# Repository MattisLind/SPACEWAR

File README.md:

# SPACEWAR

The original [Spacewar!](https://en.wikipedia.org/wiki/Spacewar!) game was written for the PDP-1 minicomputer and there were several ports to other architectures.

This port to the PDP-11 architecture was done by Bill Seiler & Larry Bryant in 1974. It was then submitted to DECUS as 11-192. 

SPACEWAR on the HP 1332A vector screen.

Click to see video clip:

SPACEWAR on a VR12 vector screen. Has a very nice P7 phosphor that has fantastic after-glow. Actually this type of phosphor was used in the PDP-1 screen which the original SPACEWAR was run on.

Ufortunatley DECUS threw away all the sources many years ago. By luck I got in contact with Bill Seiler and he sent me the source files. The sources were provided to me as scanned documents. With some help the original PDFs were tidied up to help the OCR process. Then I partly OCRed and manually transcribed all files into text files.
The files were then then fed into the PAL11-S assembler and numerous errors were detected already when trying to get the files pass the syntax check. Then the output listing files was compared side by side with the original scanned files. Byte for byte were checked and yet more problems were found. Finally during linking a number of issues with global symbols were found. In the end the program assembled and linked correctly.

As a side note there exists at least two more ports of the SPACEWAR game to the PDP-11 architecture ([for example this one](https://saildart.org/SW.P11%5B11,BO%5D)), but both of those rely on the VT11 vector drawing option which is for example present in the GT40 system. I don't have a VT11 neither a GT40 so this is my best option to get SPACEWAR on a PDP-11.

## Give it to me!

If you don't want to go down the route of assembling and linking all the source moddules there is an easy solution. Just grab the dddp.dsk image and use the TU58FS tool (or some other TU58 emulator) to serve it to your PDP-11.  It contains a bootable DDDP image with a SPACEWAR image binary image. Just type R SPCWAR.LDA and it will run provided you have the AR11 card.

## Assembling

In case you just want to run the binary and not want the fun of building it from scratch, just grab the SPACEWAR.ABS file in the ar11-patch branch (if you have a AR11 board in your machine) and run in from ~~025424~~ ~~025432 (please note that this may change since a new build of the code might affect the entrypoint, check the SPACEWAR.MAP file when in doubt). Make sure to also load the IOX binary in the IOX-11 subfolder into memory before starting the SPACEWAR and set the switch regsiter to all zeroes. I have seen that otherwise it gets stuck in the IOX library. Probably a non-zero SR indicate some options to the IOX library, but I haven't investigated that further.~~
Update: Even easier should be to use the SPACEWARWIOX.LDA binary since it includes the IOX-11 binary and also have the proper transfer address which should make the loader start it directly. Make sure to have the SR set to 0. This binary starts at 1000 if it is loaded using PDP11GUI rather than read from paper tape.

It is possible to assemble the files located in the SRC folder using PAL11-S assembler under SimH PDP-11 simulator. PAL11-S is part of the [PDP-11 Paper Tape Software](http://bitsavers.informatik.uni-stuttgart.de/www.computer.museum.uq.edu.au/pdf/DEC-11-XPTSA-B-D%20PDP-11%20Paper%20Tape%20Software%20Handbook.pdf). 

First toggle in the bootstrap loader (or use the file TOOLS/simh.ini)
```
sim> SET CPU 11/05
Disabling XQ
sim> SET CPU 16K
sim> 
sim> 
sim> ; Disable devices that we don't need
sim> SET HK DISABLE
sim> SET DZ DISABLE
sim> SET RL DISABLE
sim> SET RX DISABLE
sim> SET RP DISABLE
sim> SET RQ DISABLE
sim> SET TM DISABLE
sim> SET TQ DISABLE
sim> SET RK DISABLE
sim> 
sim> ; Enable the high-speed paper tape reader/punch
sim> SET PTR ENABLE
sim> SET PTP ENABLE
sim> DEPOSIT 037744 016701
sim> DEPOSIT 037746 000026
sim> DEPOSIT 037750 012702
sim> DEPOSIT 037752 000352
sim> DEPOSIT 037754 005211
sim> DEPOSIT 037756 105711
sim> DEPOSIT 037760 100376
sim> DEPOSIT 037762 116162
sim> DEPOSIT 037764 000002
sim> DEPOSIT 037766 037400
sim> DEPOSIT 037770 005267
sim> DEPOSIT 037772 177756
sim> DEPOSIT 037774 000765
sim> DEPOSIT 037776 177550
sim> ATTACH PTR TOOLS/DEC-11-L2PC-PO.ptap 
sim> GO 037744

HALT instruction, PC: 037500 (MOV PC,SP)
sim> D SR 37500 
sim> ATTACH PTR TOOLS/dec-uplsa-a-pl.bin 
PTR: unit is read only
sim> GO 037500

PAL-11S  V003A

*S 
```
Now pressing Ctrl-E allows for attaching the correct input and output virtual paper tapes.
```
Simulation stopped, PC: 035110 (CMPB R1,#14)
sim> attach ptr SRC/SPCWAR.PAL
sim> attach ptp OBJ/SPCWAR.OBJ
PTP: creating new file
sim> attach lpt LST/SPCWAR.LST
LPT: creating new file
sim> c
```
Now we are back in the PAL11-S assmebler. But it has alread greated you above with an S(ource) so it won't do that again. Simply type H for input via High-Speed reader. The same for the O(utput). Send L(ist) to the P(rinter) and the T(able) to the T(eletype) output.
```
H

*B H

*L P

*T T

 ADBR   = 176772 G     ADCS   = 176770 G     AMMO     000216RG  
 ANGH1    000154RG     ANGH2    000202RG     ANGL1    000152RG  
 ANGL2    000200RG     ANGMID = 000702 G     COMPAR = ****** G  
 DAC0   = 176750 G     DAC1   = 176752 G     DAC2   = 176754 G  
 FIRE   = 001440 G     FLAG1    000132RG     FLAG2    000160RG  
 GAME1    000222RG     GAME2    000224RG     GRAVTY = ****** G  
 GRVFLG   000226RG     HIT1     000204RG     HIT2     000206RG  
 MASK   = 002100 G     PARM   = ****** G     PC     =%000007    
 POINT  = ****** G     PTNUM  = ****** G     PTREP    000230RG  
 RESET  = ****** G     RKTSIZ = 007000 G     RKT1   = ****** G  
 RKT2   = ****** G     R0     =%000000       R1     =%000001    
 R2     =%000002       R3     =%000003       R4     =%000004    
 R5     =%000005       R6     =%000006       R7     =%000007    
 SHOTS1   000210RG     SHOTS2   000212RG     SP     =%000006    
 SPCRST   000020RG     SPCWAR   000000RG     SPC01    000066R   
 SUNSZ  = 004000 G     TSPEED   000220RG     UPDAT1 = ****** G  
 UPDAT2 = ****** G     WIN      000214RG     XDISP1   000150RG  
 XDISP2   000176RG     XSIZE1   000142RG     XSIZE2   000170RG  
 XVELH1   000146RG     XVELH2   000174RG     XVELL1   000144RG  
 XVELL2   000172RG     YDISP1   000140RG     YDISP2   000166RG  
 YSIZE1   000130RG     YSIZE2   000156RG     YVELH1   000136RG  
 YVELH2   000000RG     YVELL1   000134RG     YVELL2   000162RG  
 .      = 000232R     

 END ?
```

So now the assembler want to run the second pass which means that we have to load our virtual source tape again. Press Ctrl-E now to get into SimH.
```
Simulation stopped, PC: 035464 (BR 35334)
sim> attach ptr SRC/SPCWAR.PAL
sim> c
```
And then press return when back into the PAL11-S environment.

```

000000 ERRORS

PAL-11S  V003A

*S 
```
Do this for each and every file to produce object files.

## Linking

Linking involves running the LINK11-S which is similar to how to run the assembler.
```
sim> SET CPU 11/05
Disabling XQ
sim> SET CPU 16K
sim>  
sim> ; Disable devices that we don't need
sim> SET HK DISABLE
sim> SET DZ DISABLE
sim> SET RL DISABLE
sim> SET RX DISABLE
sim> SET RP DISABLE
sim> SET RQ DISABLE
sim> SET TM DISABLE
sim> SET TQ DISABLE
sim> SET RK DISABLE
sim> 
sim> ; Enable the high-speed paper tape reader/punch
sim> SET PTR ENABLE
sim> SET PTP ENABLE
sim> DEPOSIT 037744 016701
sim> DEPOSIT 037746 000026
sim> DEPOSIT 037750 012702
sim> DEPOSIT 037752 000352
sim> DEPOSIT 037754 005211
sim> DEPOSIT 037756 105711
sim> DEPOSIT 037760 100376
sim> DEPOSIT 037762 116162
sim> DEPOSIT 037764 000002
sim> DEPOSIT 037766 037400
sim> DEPOSIT 037770 005267
sim> DEPOSIT 037772 177756
sim> DEPOSIT 037774 000765
sim> DEPOSIT 037776 177550
sim> ATTACH PTR TOOLS/DEC-11-L2PC-PO.ptap 
sim> GO 037744

HALT instruction, PC: 037500 (MOV PC,SP)
sim> ATTACH PTR TOOLS/dec-11-ulksa-a-pl.bin 
PTR: unit is read only
sim> D SR 0
sim> GO 037500

LINK-11S V002A
*I H

*O H

*M P

*T 

*B 

PASS 1

* 
Simulation stopped, PC: 035140 (MOV R5,14(SP))
sim> ATTACH PTP SPACEWAR.ABS
sim> ATTACH LPT SPACEWAR.MAP
sim> ATTACH PTR OBJ/SPCWAR.OBJ 
```
To the linker you specify the I(input) and O(utput) deivce. H (High-speed) reader or L (Low-speed). Load map (M) is either not generated at all if pressing RETURN or by pressing H (High speed punch) or T(teletype), or P(Line Printer). The there are two questions (T and B) how the relocation should be done. Press RETURN for top of memory to both of those.

In this case I have chosen to have the resulting binary to be generated on the paper tape punch and the module map on the line printer.

After this each file is fed into the linker by attaching it to the reader and pressing RETURN at the * prompt. When all object files has been presented to the first pass of the linker you can press U a the * prompt to show the remaining undefined symbols. When all is done press E and the linker will print the load map and then start the seconds pass, requesting the same object files in the same order.

```
* U

* E

PASS 2

* 
Simulation stopped, PC: 035122 (ADD #34662,R2)
sim> ATTACH PTR FPMP-11/FPMP-11-SPACEWAR.OBJ
sim> c
```

When you supplied the last file you should be greated with another linker startup message.

```
LINK-11S V002A
*I 
```
Then you know that all is good and there should be a binary file and map file generated.

The first time I tried to run the linker was not succesful. After feeding all source modules unfortunatley I got two undefined symbols.
```
sim> c

* U
$ICI  
$ICO  

* 
```

These two subroutines are from the FPMP-11 package. Just adding one of the two pre-made FPMP-11 object files does not resolve the two undefined symbols.
[FPMP-11 documentation.](http://bitsavers.informatik.uni-stuttgart.de/www.computer.museum.uq.edu.au/pdf/DEC-11-NFPMA-C-D%20FPMP-11%20User's%20Manual.pdf)

Reading the manual a bit more revealed that the reason is that the two premade object files just contain a subset of the FPMP-11 package, not the $ICI and $ICO modules! To get those into the build one has to add a special file with defines for two variables used by the conditional build of the FPMP-11 packaged. By feeding this file
```
;******************************************************
;
;               CONDITIONAL SWITCHES 
;               FOR FPMP-11 PACKAGE
;               WHEN USED WITH SPACE WAR
;
       CND$24=1
       CND$25=1
       .EOT
```
before the six FPMP-11 source files I had a tailor made object paper tape with just the $ICI and $ICO symbols defined! 

Please note that the SPCWAR module has to be the first module and the POINT module the last module. See comments further below. All the other modules comes inbetween including the FPMP-11 library built previously.
 
~~This new object tape was then fed first into the linker, followed by all the 19 object paper tapes of SPACE WAR ending with the module POINT which has to be the last module.~~ And indeed the link completeted without any unresolved symbols this time.
This was the resulting MODULE MAP from LINK11-S:
```
* U

* E

LOAD MAP

TRANSFER ADDRESS: 000001
LOW LIMIT: 025424
HIGH LIMIT: 037460
**********
MODULE  SPCWAR
SECTION ENTRY   ADDRESS SIZE
<. ABS.>        000000  000000
<      >        025424  000232
        ADBR    170402
        ADCS    170400
        AMMO    025642
        ANGH1   025600
        ANGH2   025626
        ANGL1   025576
        ANGL2   025624
        ANGMID  000702
        DAC0    170412
        DAC1    170414
        DPCS    170410
        ERASE   010000
        FIRE    001440
        FLAG1   025556
        FLAG2   025604
        GAME1   025646
        GAME2   025650
        GRVFLG  025652
        HIT1    025630
        HIT2    025632
        MASK    002100
        PTREP   025654
        RKTSIZ  007000
        SHOTS1  025634
        SHOTS2  025636
        SPCRST  025444
        SPCWAR  025424
        SUNSZ   004000
        TSPEED  025644
        WIN     025640
        XDISP1  025574
        XDISP2  025622
        XSIZE1  025566
        XSIZE2  025614
        XVELH1  025572
        XVELH2  025620
        XVELL1  025570
        XVELL2  025616
        YDISP1  025564
        YDISP2  025612
        YSIZE1  025554
        YSIZE2  025602
        YVELH1  025562
        YVELH2  025610
        YVELL1  025560
        YVELL2  025606
**********
MODULE  CHAR  
SECTION ENTRY   ADDRESS SIZE
<      >        025656  000302
        CHAR    025656
**********
MODULE  CHRTAB
SECTION ENTRY   ADDRESS SIZE
<      >        026160  000606
        CHRTAB  026160
**********
MODULE  COMPAR
SECTION ENTRY   ADDRESS SIZE
<      >        026766  000444
        COMPAR  026766
**********
MODULE  EXPLOD
SECTION ENTRY   ADDRESS SIZE
<      >        027432  000330
        EXPLOD  027432
        EXPREP  027550
        EXPX    027556
        EXPY    027560
**********
MODULE  GRAVTY
SECTION ENTRY   ADDRESS SIZE
<      >        027762  000450
        GRAVTY  027762
**********
MODULE  MULPLY
SECTION ENTRY   ADDRESS SIZE
<      >        030432  000304
        MULPLY  030432
**********
MODULE  PARM  
SECTION ENTRY   ADDRESS SIZE
<      >        030736  001214
        PARM    030736
**********
MODULE  PWRUP 
SECTION ENTRY   ADDRESS SIZE
<      >        032152  000106
**********
MODULE  RESET 
SECTION ENTRY   ADDRESS SIZE
<      >        032260  000206
        CENTER  040000
        ORBIT   000400
        RESET   032260
        RES01   032446
**********
MODULE  RKT1  
SECTION ENTRY   ADDRESS SIZE
<      >        032466  000160
        RKT1    032466
**********
MODULE  RKT2  
SECTION ENTRY   ADDRESS SIZE
<      >        032646  000142
        RKT2    032646
**********
MODULE  SCORE 
SECTION ENTRY   ADDRESS SIZE
<      >        033010  000266
        SCORE   033010
**********
MODULE  SINCOS
SECTION ENTRY   ADDRESS SIZE
<      >        033276  000462
        SINCOS  033276
**********
MODULE  SLINE 
SECTION ENTRY   ADDRESS SIZE
<      >        033760  000140
        SLINE   033760
**********
MODULE  SUN   
SECTION ENTRY   ADDRESS SIZE
<      >        034120  000304
        SUN     034120
**********
MODULE  UPDAT1
SECTION ENTRY   ADDRESS SIZE
<      >        034424  000372
        UPDAT1  034424
**********
MODULE  UPDAT2
SECTION ENTRY   ADDRESS SIZE
<      >        035016  000372
        UPDAT2  035016
**********
MODULE  FPMP11
SECTION ENTRY   ADDRESS SIZE
<      >        035410  000640
        $ERR    036212
        $ERRA   036222
        $ERVEC  036242
        $ICI    035416
        $ICO    035722
        $OCI    035410
        $OCO    035714
        $POLSH  036206
        $V20A   036206
**********
MODULE  POINT 
SECTION ENTRY   ADDRESS SIZE
<      >        036250  001210
        POINT   036250
        PTNUM   036456
PASS 2

* 
```
And it also resulted a 7323 byte file in Absolute Binary format! From the load map one can deduce the starting address of the binary. 025424 in this case.

### Full linking transcript

This the full transcript on how to link the SPACEWARWIOX.LDA binary. At the B prompt give 1000 to indicate that the starting address should be 1000 octal.

```
$ ~/simh/BIN/pdp11 

PDP-11 simulator V4.0-0 Beta        git commit id: f1a6d538
sim> do TOOLS/simh.ini
Disabling XQ

HALT instruction, PC: 037500 (MOV PC,SP)
sim> ATTACH PTR TOOLS/dec-11-ulksa-a-pl.bin 
sim> D SR 0
sim> GO 037500

LINK-11S V002A
*I H

*O H

*M P

*T 

*B 1000

PASS 1

* 
Simulation stopped, PC: 035122 (ADD #34662,R2)
sim> attach ptp SPACEWARWIOX.LDA
PTP: creating new file
sim> attach LPT SPACEWARWIOX.MAP
LPT: creating new file
sim> ATTACH PTR OBJ/SPCWAR.OBJ
sim> c

* 
Simulation stopped, PC: 035042 (MOV (SP)+,R5)
sim> ATTACH PTR FPMP-11/FPMP-11-SPACEWAR.OBJ
sim> c

* 
Simulation stopped, PC: 035036 (CLR R4)
sim> ATTACH PTR OBJ/CHAR.OBJ
sim> c

* 
Simulation stopped, PC: 035104 (CMPB R1,#14)
sim> ATTACH PTR OBJ/CHRTAB.OBJ
sim> c

* 
Simulation stopped, PC: 035110 (BHI 35354)
sim> ATTACH PTR OBJ/COMPAR.OBJ
sim> c

* 
Simulation stopped, PC: 035450 (JSR R4,35462)
sim> ATTACH PTR OBJ/EXPLOD.OBJ
sim> c

* 
Simulation stopped, PC: 035054 (MOV (SP)+,R0)
sim> ATTACH PTR OBJ/GRAVTY.OBJ
sim> c

* 
Simulation stopped, PC: 035122 (ADD #34662,R2)
sim> ATTACH PTR OBJ/MULPLY.OBJ
sim> c

* 
Simulation stopped, PC: 035140 (MOV R5,14(SP))
sim> ATTACH PTR OBJ/PARM.OBJ
sim> c

* ATTACH PTR OBJ/PWRUP.OBJ\\\\\\\\\\\\\\\\\\\\\\\\
Simulation stopped, PC: 035342 (ADD (SP)+,PC)
sim> ATTACH PTR OBJ/PWRUP.OBJ
sim> c

* 
Simulation stopped, PC: 035026 (MOV R3,-(SP))
sim> ATTACH PTR OBJ/RESET.OBJ
sim> c

* 
Simulation stopped, PC: 035342 (ADD (SP)+,PC)
sim> ATTACH PTR OBJ/RKT1.OBJ
sim> c

* 
Simulation stopped, PC: 035056 (RTI)
sim> ATTACH PTR OBJ/RKT2.OBJ
sim> c

* 
Simulation stopped, PC: 035460 (BR 35330)
sim> ATTACH PTR OBJ/SCORE.OBJ
sim> c

* 
Simulation stopped, PC: 032100 (BIT (R0)+,@4(SP))
sim> ATTACH PTR OBJ/SINCOS.OBJ
sim> c

* 
Simulation stopped, PC: 035110 (BHI 35354)
sim> ATTACH PTR OBJ/SLINE.OBJ
sim> C

* 
Simulation stopped, PC: 035336 (MOVB 34641(R1),(SP))
sim> ATTACH PTR OBJ/SUN.OBJ
sim> C

* 
Simulation stopped, PC: 035332 (ASL R1)
sim> ATTACH PTR OBJ/UPDAT1.OBJ
sim> C

* 
Simulation stopped, PC: 035336 (MOVB 34641(R1),(SP))
sim> ATTACH PTR OBJ/UPDAT2.OBJ
sim> C

* 
Simulation stopped, PC: 035100 (MOVB (R5)+,R1)
sim> ATTACH PTR IOX-11/dec-11-xioxa-a.obj
sim> C

* U
POINT 
PTNUM 

* 
Simulation stopped, PC: 035162 (BLE 35332)
sim> ATTACH PTR OBJ/POINT.OBJ
sim> C

* U

* E

PASS 2

* 
Simulation stopped, PC: 035046 (MOV (SP)+,R3)
sim> ATTACH PTR OBJ/SPCWAR.OBJ
sim> C

* 
Simulation stopped, PC: 035460 (BR 35330)
sim> ATTACH PTR FPMP-11/FPMP-11-SPACEWAR.OBJ
sim> C

* 
Simulation stopped, PC: 035150 (BLE 35332)
sim> ATTACH PTR OBJ/CHAR.OBJ
sim> C

* 
Simulation stopped, PC: 035150 (BLE 35332)
sim> ATTACH PTR OBJ/CHRTAB.OBJ
sim> C

* 
Simulation stopped, PC: 035120 (BNE 35352)
sim> ATTACH PTR OBJ/COMPAR.OBJ
sim> C

* 
Simulation stopped, PC: 035120 (BNE 35352)
sim> ATTACH PTR OBJ/EXPLOD.OBJ
sim> C

* 
Simulation stopped, PC: 035034 (CLR R3)
sim> ATTACH PTR OBJ/GRAVTY.OBJ
sim> C

* 
Simulation stopped, PC: 035112 (MOVB (R5)+,R2)
sim> ATTACH PTR OBJ/MULPLY.OBJ
sim> C

* 
Simulation stopped, PC: 035100 (MOVB (R5)+,R1)
sim> ATTACH PTR OBJ/PARM.OBJ
sim> C

* 
Simulation stopped, PC: 035114 (BIT #177770,R2)
sim> ATTACH PTR OBJ/PWRUP.OBJ
sim> C

* 
Simulation stopped, PC: 035154 (BLE 35346)
sim> ATTACH PTR OBJ/RESET.OBJ
sim> C

* 
Simulation stopped, PC: 035154 (BLE 35346)
sim> ATTACH PTR OBJ/RKT1.OBJ
sim> C

* 
Simulation stopped, PC: 035154 (BLE 35346)
sim> ATTACH PTR OBJ/RKT2.OBJ
sim> C

* 
Simulation stopped, PC: 035040 (MOV R0,PC)
sim> ATTACH PTR OBJ/SCORE.OBJ
sim> C

* 
Simulation stopped, PC: 035154 (BLE 35346)
sim> ATTACH PTR OBJ/SINCOS.OBJ
sim> C

* 
Simulation stopped, PC: 035162 (BLE 35332)
sim> ATTACH PTR OBJ/SLINE.OBJ
sim> C

* 
Simulation stopped, PC: 035066 (JSR R0,35022)
sim> ATTACH PTR OBJ/SUN.OBJ
sim> C

* 
Simulation stopped, PC: 035022 (MOV R1,-(SP))
sim> ATTACH PTR OBJ/UPDAT1.OBJ
sim> C

* 
Simulation stopped, PC: 035032 (MOV R5,-(SP))
sim> ATTACH PTR OBJ/UPDAT2.OBJ
sim> C

* 
Simulation stopped, PC: 035126 (MOVB (R2),R3)
sim> ATTACH PTR IOX-11/dec-11-xioxa-a.obj
sim> C

* ATTACH PTR OBJ/POINT.OBJ\\\\\\\\\\\\\\\\\\\\\\\\
Simulation stopped, PC: 035150 (BLE 35332)
sim> ATTACH PTR OBJ/POINT.OBJ
sim> C

LINK-11S V002A
*I 
Simulation stopped, PC: 035112 (MOVB (R5)+,R2)
sim> DETACH PTP
sim> DETACH PTR
sim> DETACH LPT
sim> 

```

If you feed the wrong module in the second pass this message will be shown. Just feed the correct module and try again.

```
Simulation stopped, PC: 035046 (MOV (SP)+,R3)
sim> ATTACH PTR OBJ/SLINE.OBJ
sim> C

?LOAD SINCOS NEXT!
```

### Automatic start

The Abolute loader format can specify the starting address so that when the loader loads the tape (or file) into memory it will automatically jump to the starting address. This is done by specifying the starting address on the .END directive. I modified the SPCWAR.PAL file to include the starting symbol SPCWAR.

### IOX library 

The SPACE WAR program make use of the IOX-11 package for teletype IO, which means that this has to be loaded before the SPACE WAR program. Since the IOX package make use of the IOT instruction for all operations there is no linking needed. But the address of the IOX package has to not collide with the SPACE WAR program itself address space wise. It appears that the IOX-11 pacakge is fixed at 015100. ~~There are no instruction on how to assemble the package and a try in PAL-11S results in 245 errors. The IOX-11 package is an absolute binary and is loaded by the abolute loader as most other programs.~~

Later on I learnt that IOX-11 is supposed to be built with PAL-11A instead of PAL-11S. PAL-11A reads the two files directly after each other. There are a number of .EOT directives that will give a EOF? prompt in the assembler. Just pressing CR will feed to the next section. The idea behind this is that if one want to modify the start address of join other source files this can be done at these points. However I wanted to make a single SPACEWAR binary with IOX builtin that is loaded into the machine. Thus I needed to use PAL-11S which is used for the rest of SPACEWAR. There are some things that differ since PAL-11S is a relocating assembler and PAL-11A is a absolute assembler. I had to add .CSECT and .ASECT directives to the source. I also combined the module into one source file.

With this in place it was possible to re-link the entire package.

## A disk image with SPACEWAR

I thought it would be good to have a disk image with the SPACEWAR binary loaded. Using the xxdpdir utilities bye Dan North I added the binary to the image. The image with the SPACEWAR binary is provided as a TU58 disk image, dddp.dsk. The image has a XXDP+ system on it.

~~The intention is that it should be possible to simply do a RUN SPCWAR.LDA from the XXDP+ prompt but it does not appear to work. It gets stuck inside the IOX-library waiting for something, at least when testing this in SIMH. But if I halt the SIMH simulator and do a RESET command followed by GO 1000, it is actually runs. So somehow the RESET command in SimH circumvents the problem. I have not figured out how to solve this. I was thinking that a RESET instructon could do the same thing. But haven't tried it yes.~~

It suddenly occured to me that the reason for not working was a simple as interrupts. The XXDP monitor runs with interrups disabled. The RESET command and the START switch on the real machine resets interrup level. By lowering the priority level of the CPU it worked just fine. The dddp.dsk is a TU58 image which is bootable. A simple RUN SPCWAR.LDA will start SPCWAR. For my own use I will make a CAPS-11 cassette and possibly also a TADP cassette with the SPCWAR.LDA binary.

With the SPACEWAR binary on the dddp.dsk it is possible to boot a PDP-11 into the XXDP monitor with a second serial card using a TU58 emulator. This second serial port has to be setup with base address 176500 and vector 300. Make sure it is set to 8 bits without parity. Jörg Hoppe has designed a such an emulator which is combined with a method for downloading the bootstrap using the console emulator called [tu58fs](http://retrocmp.com/tools/tu58fs).

Start an emulation process over /dev/ttyUSB0 running at 9600 bps for drive 0 in readonly mode using dddp.dsk image
```
tu58fs -p /dev/ttyUSB0 -b 9600 -d 0 r dddp.dsk
```

Command to download and start a boostrap process over /dev/ttyUSB1 running at 2400 bps using a m9301 board in the pdp-11.
```
tu58fs -p /dev/ttyUSB1 -b 2400 --boot m9301 1
```
When XXDP has greeted you with a startup message and you got the . prompt it is possible to simply run the binary. It takes some time to loads since it does this over a 9600 bps serial line so have a bit of patience.
```
.RUN SPCWAR.LDA
```
After a while SPACEWAR will start.

## Running SPACE WAR

All this made it possible to build a new SPACEWAR binary with the IOX library built in and also have the autostart feature. The new binary is called SPACEWARWIOX.LDA.
The extension .LDA is to signify that it should be possible to use this from any PDP-11 oprating system that is able to load abolute binary files. For example XXDP is able to handle .LDA files and I think CAPS-11 and DOS-11 too.

```
sim> SET CPU 11/05
Disabling XQ
sim> SET CPU 16K
sim> 
sim> ; Disable devices that we don't need
sim> SET HK DISABLE
sim> SET DZ DISABLE
sim> SET RL DISABLE
sim> SET RX DISABLE
sim> SET RP DISABLE
sim> SET RQ DISABLE
sim> SET TM DISABLE
sim> SET TQ DISABLE
sim> SET RK DISABLE
sim> 
sim> ; Enable the high-speed paper tape reader/punch
sim> SET PTR ENABLE
sim> SET PTP ENABLE
sim> DEPOSIT 037744 016701
sim> DEPOSIT 037746 000026
sim> DEPOSIT 037750 012702
sim> DEPOSIT 037752 000352
sim> DEPOSIT 037754 005211
sim> DEPOSIT 037756 105711
sim> DEPOSIT 037760 100376
sim> DEPOSIT 037762 116162
sim> DEPOSIT 037764 000002
sim> DEPOSIT 037766 037400
sim> DEPOSIT 037770 005267
sim> DEPOSIT 037772 177756
sim> DEPOSIT 037774 000765
sim> DEPOSIT 037776 177550
sim> ATTACH PTR TOOLS/DEC-11-L2PC-PO.ptap 
sim> GO 037744

HALT instruction, PC: 037500 (MOV PC,SP)
sim> d sr 0
sim> ATTACH PTR IOX-11/dec-11-xioxa-a-pb.bin 
sim> GO 037500

HALT instruction, PC: 037712 (BR 37514)
sim> ATTACH PTR SPACEWAR.ABS 
sim> GO 037500

HALT instruction, PC: 037712 (BR 37514)
sim> GO 034604

SPACE WAR
ANY CHANGES? (YES-NO)
Y
WANT A SUN WITH GRAVITY? (YES-NO)
Y
WANT REAPPEARING PHOTON TORPEDSOES? (YES-NO)
Y
INPUT # OF TORPEDOS RKTS WILL HAVE. STD=64
64
INPUT # OF HITS TO DESTROY A RKT  STD=32
32
INPUT SPEED OF TORPEDOES. STD=16000
16000

HALT instruction, PC: 000042 (BIC R4,SP)
sim>
```
So why is it halting? There is a Non existing memory (NXM) handler installed by the IOX-11 package.
```
sim> e 0-200
0:	000000
2:	000000
4:	015604
6:	000340
10:	000000
12:	000000
14:	000000
16:	000000
20:	015256
22:	000340
24:	032662
26:	000340
30:	000000
32:	000000
34:	000000
36:	000000
40:	000000
42:	040406
44:	000000
46:	000000
50:	000000
52:	000000
54:	000000
56:	000000
60:	016040
62:	000200
64:	016672
66:	000200
70:	016132
72:	000200
74:	017056
76:	000200
```
Location 4 is the NXM trap handler and the handler is located at address 15604. Then there are handlers for the paper taper reader, the tty keybaord and printer etc. 

A breakpoint in SimH at that address show that the SP is pointing to 
```
sim> break 15604
sim> go 034604

SPACE WAR
ANY CHANGES? (YES-NO)
Y
.
.
.
Breakpoint, PC: 015604 (JSR R0,15220)
sim> e sp
SP:	034600
```
Now checking the stack at this SP value:
```
sim> e 34600
34600:	034632
```
So the Stack contain the PC of the next instruction after the one causing the NXM trap. 
```
e -m 34624-34700
34624:	MOV #401,176770
34632:	MOV 35020,35010
34640:	MOV 35020,35012
34646:	MOV 35022,35014
34654:	MOV 35022,35016
34662:	CLR 36456
34666:	JSR PC,32770
34672:	MOV #34734,R2
34676:	JSR PC,35342
```
So the offending instruction is the one at 34624 which is trying to reference the ADCS register at address 176770. And since this device is not implemented in SimH this address will not respond and thus the NXM trap!

The code at 15604 will subsequently make a JMP to address 40 where the HALT instruction is executed. Thus stopping the processor.
```
15600:	JMP 40
15604:	JSR R0,15220
15610:	CLR R0
15612:	MOV 14(SP),R1
15616:	BR 15600
```

Then when I had installed the correct hardware and patched the source to use AR11 it still failed. Then I discovered that the stackpointer is initialized with the SPCWAR symbol. Meaning that it grows downwards from that point. Not having the SPCWAR module as the first module will then be a problem since the stack will overwrite the code. I.e. The SPCWAR module has to be the first module and the POINT module has to be that last module. Otherwise the order is of no importance.

## Adaptations to the AR11

Since I don't have any [AD01](http://manx-docs.org/collections/hcps/AD01_manual.pdf) neither any [AA11](http://manx-docs.org/collections/hcps/AA11-D_manual.pdf) subsystem for my PDP-11 and the objective is to have the program running on as like hardware as possible I have to modify it to the hardware I do have, which is the AR11. One obvious benefit of the AR11 is that it is a single HEX module compared with the AD01 and AA11 which are bulky rack-mount system units as big as the computer it self (PDP-11/10).

One disadvantage is that the [AR11](http://bitsavers.trailing-edge.com/pdf/dec/unibus/AR11_UsersMan.pdf) is 10 bit only, meaning that som small changes has to be done to handle 12 vs 10 bits.

One obvious difference is that the AR11 make use of completely different IO address. The definitions of the DAC0, DAC1, DAC2, ADCS and ADBR has to change. The use of DAC2 is a little bit peculiar. The DAC2 is used for the Z-axis of the X-Y-scope and the only bit that is used is the MSB which is changed from off to on and the off to signify a dot. The AR11 doesn't have a third DAC at all. Instead it have one single bit called Intensify in the control status register. It makes sense to use this bit instead. But at least the character drawing routine in CHAR.PAL will turn on Z-axis and then change the X and Y coordinates when drawing a character. When done with each character it will switch off the Z-axis. This means that the intensify pulse cannot be used. Instead one of the logical signals will be used to control the Z-axis. 

Another issue is that the oscilloscope screens requires certain time to deflect the beam. The AR11 include a functionality that when setting the intensify bit it will delay the acutual intensify operation 20 us and then issue a 2 us pulse. The AR11 will then signal back a DONE flag to indicate that next dot can be painted on screen. The SPACEWAR code does not wait for any DONE flag but draws as fast as the CPU can. This may be ok for a PDP-11/10 but might be to fast for a 11/45? And it may be too fast for certain oscilloscope hardware but OK for others.

I ended up using the ERASE (12) bit in the display status register to control the Z-axis. It is a open collector signal so there need to be a pull up resistor in the end of the line at the Z-input of the scope. I also discovered that the AA11 subsystem is 2's complment while the AR11 is not. So besides shifting the output value two steps to the right to make it fit into a ten bit number I also had to add 512 to the number before sending it off to the D/A converter.

The AD01 is 10 bit so there were very few changes appart from changing addresses, except for one thing. The AR11 has to be put into unipolar mode since the potentiometers of the joysticks are fed from the internal 5V source of the board.

All adaptations for the AR11 went into a branch called ar11-patch. Make sure to get that one.

## Joysticks

Instructions for building the Joysticks can be found [here](/joystick/README.md). Or look in the "joystick" folder.

## Cable harness (No longer recommended, See Breakout board)

I used 47217-000LF/48254-000LF contact elements and 65043-015LF contact housings. The cable is a three pair shieled cable for the Joysticks and the X, Y and Z inputs. An extra cable of simpler type was used for the intensify signal in case I ever wanted to use it.

|  Pin |  Signal   |  Connect to  |
|------|-----------|--------------|
|  A   | WRITH THRU L |  NC       |
|  B   | DISP CH02 L  |  Pull up to 5V in the scope end + Z input of scope        |
|  C   | ERASE L      |  NC  |
|  D   | INTESIFY     |  Optional Z input if the standard point plotting mechanism of the AR11 is to be used for other purposes. |
|  E   | NON-STORE L  |  NC     |
|  F   | X OUT        |  Scope X input |
|  H   | ERASE RET L  |  NC |
|  J   | Y OUT        |  Scope Y input |
|  K   | Analog ground | ground for X and Y twisted pair. Including shield |
|  L   |  A/D CH 17 input | NC |
|  M   | Analog ground | NC |
|  N   |  A/D CH 16 input | NC |
|  P   | Logic ground  |  Z - axis pair ground and sheild |
|  R   |  A/D CH 15 input | NC |
|  S   | Logic ground  |  Intensify Z- axis pair return and shield (optional) |
|  T   | A/D CH 14 input | NC |
|  U   | EXT AD ST L |   NC |
|  V   | A/D CH 13 input | NC |
|  W  | Analog ground | NC |
|  X   | A/D CH 12 input | NC |
|  Y  | Analog ground | NC |
|  Z   | A/D CH 11 input | NC |
|  AA  | Analog ground | NC |
|  BB   | A/D CH 10 input | NC |
|  CC  | Analog ground | NC |
|  DD   | A/D CH 7 input | NC |
|  EE  | Analog ground | Joystick 2 Acceleration pot ground and shield |
|  FF   | A/D CH 6 input | NC |
|  HH  | Analog ground | Joystick 2 Angle pot ground and shield |
|  JJ   | A/D CH 5 input | NC |
|  KK  | Analog ground | Joystick 1 Acceleration pot ground and shield |
|  LL   | A/D CH 4 input | NC |
|  MM  | Analog ground | Joystick 1 Angle pot ground and shield |
|  NN   | A/D CH 3 input | Joystick 2 Acceleration pot viper |
|  PP  | -14V HQ | NC |
|  RR   | A/D CH 2 input | Joystick 2 Angle pot viper |
|  SS  | +14V HQ| NC |
|  TT   | A/D CH 1 input | Joystick 1 Acceleration pot viper |
|  UU  | +5V output | Power to feed joysticks and pull-up resistor for Z-axis |
|  VV   | A/D CH 0 input | Joystick 1 Angle pot viper |

## Breakout board

Over time the 40 pin connector with crimped contact elemnts started to become a problem. It was bulky and thick and hard to get in and out the machine. I designed a breakout board that attached via a 40 pin flat cable instead. This breakout board has three connectors. One for each joustick and one for the screen.

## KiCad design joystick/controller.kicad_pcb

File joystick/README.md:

# Joystick Controller #
Here is the needed information to build a basic joystick.

## Bill of Materials ##
 * Project Box (115 x 90 x 55mm) - [Aliexpress Link](https://www.aliexpress.com/item/4001192554657.html)
 * Cable Strain Relief (4.5mm-7.8mm Dia) - [Aliexpress Link](https://www.aliexpress.com/item/1005006247492520.html)
 * Arcade Push Button - [Aliexpress Link](https://www.aliexpress.com/item/32855254679.html)
 * Joystick (JH-D202X-R2 5K 50°)
 * 2x Resistor - 2.2K
 * 4 Core Wire (I used 5 core)
 * DB9 Connector and Housing

## Selection of a Joystick ##
There are quite a few options to choose from, and sometimes the specifications are difficult to find.
This set up has been tested with a joystick that uses potentiometers with the range of 0 to 5kOhm and a range of 50°.

Searching JH-D202X on Aliexpress should provide you with several options to pick from.

## Assembly ##

### Case ###
The case is a little tight, so spend some time to work out where you want to place things.
Take care to allow space for the nut that holds the button.
I have included some KiCad files I used to laser cut holes into the project box (see cut_template_files).
You should be able to print them in paper and use them as a template or just for some dimensions.
Mount the cable, strain relief and push button.

### Wiring ###
In my case I have use the following assignments:
 * Red - 5v
 * Green - Acceleration
 * Brown - Angle
 * White - Ground

On the DB9 Connector I have used the following:
 * Pin 4 - Red - 5v
 * Pin 1 - Green - Acceleration
 * Pin 7 - Brown - Angle
 * Pin 8 - White - Ground

If you build the controller and find that Acceleration and Angle are swapped you CAN"T just swap the Acceleration and Angle wires.
This is because the the fire button is connected to the Acceleration signal. Instead you must rotate the joystick.

### Joystick ###
> Take note of the orientation of the joystick relative to the case, otherwise you may find your controls are backwards!

Before you start make sure you joystick and button fit in the case.
Also make sure you have feed cable through the project box before soldering it to the PCB.

 1. Add the two resistors to the PCB.
 2. Glue the PCB to the bottom of the joystick (I used super glue)
 3. Solder in the potentiometers using loops of wire, allow slack so the potentiometer can be adjusted
 4. Solder in the "Fire" button (the polarity doesn't matter)
 5. Solder in the 4 cables (allow plenty of slack)
 6. Mount the Joystick to the lid

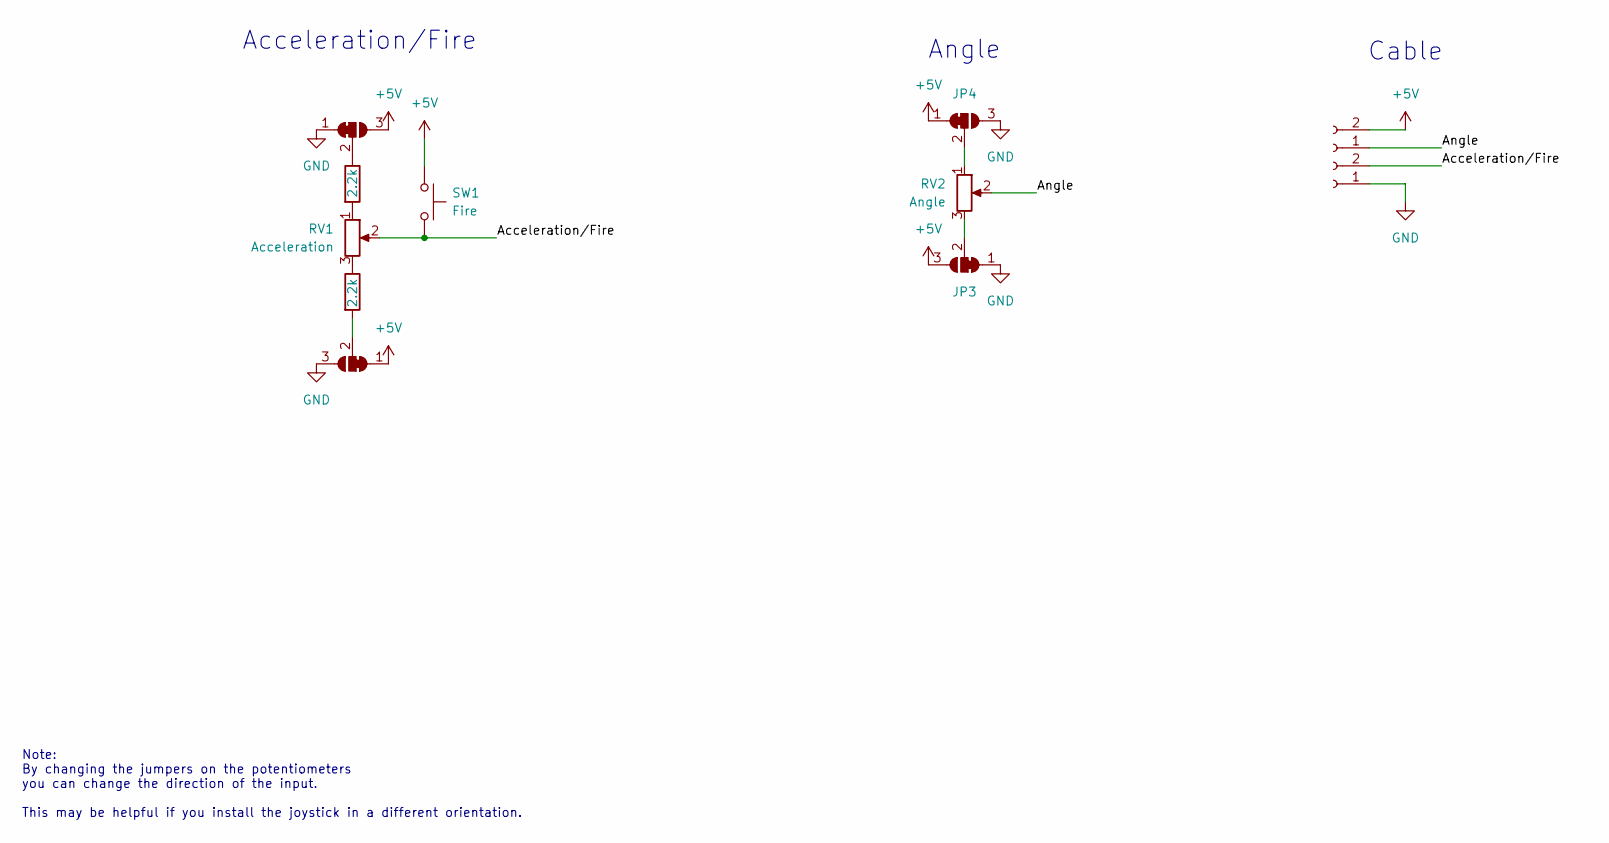
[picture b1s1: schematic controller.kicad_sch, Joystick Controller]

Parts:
J1, J2: Conn_01x02_Socket; SolderWire-0.5sqmm_1x02_P4.8mm_D0.9mm_OD2.3mm
JP1, JP2, JP3, JP4: SolderJumper_3_Bridged12; SolderJumper-3_P1.3mm_Bridged12_RoundedPad1.0x1.5mm
R1, R2: 2.2k; R_Axial_DIN0204_L3.6mm_D1.6mm_P7.62mm_Horizontal
RV1: Acceleration; Potentiometer_Piher_PC-16_Single_Horizontal
RV2: Angle; Potentiometer_Piher_PC-16_Single_Horizontal
SW1: Fire; SolderWire-0.5sqmm_1x02_P4.8mm_D0.9mm_OD2.3mm

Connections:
+5V: J1.2, JP1.1 (A), JP2.3 (B), JP3.3 (B), JP4.1 (A), SW1.1
/Acceleration/Fire: J2.2, RV1.2, SW1.2
/Angle: J1.1, RV2.2
GND: J2.1, JP1.3 (B), JP2.1 (A), JP3.1 (A), JP4.3 (B)
unnamed: JP1.2 (C), R2.2
unnamed: JP2.2 (C), R1.1
unnamed: JP3.2 (C), RV2.3
unnamed: JP4.2 (C), RV2.1
unnamed: R1.2, RV1.1
unnamed: R2.1, RV1.3

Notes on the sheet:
Note: By changing the jumpers on the potentiometers you can change the direction of the input. This may be helpful if you install the joystick in a different orientation.
Angle
Cable
Acceleration/Fire

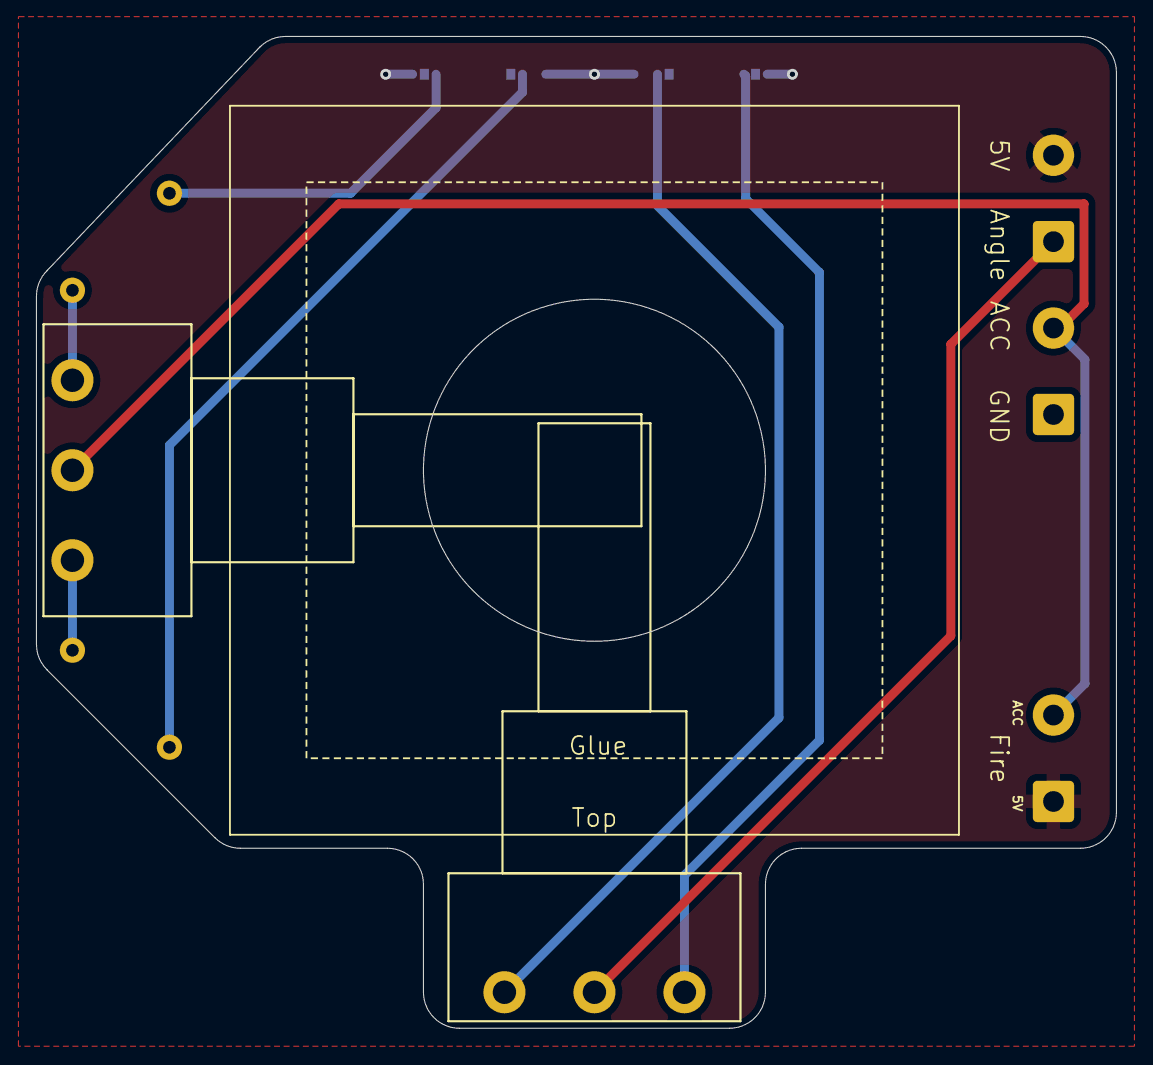
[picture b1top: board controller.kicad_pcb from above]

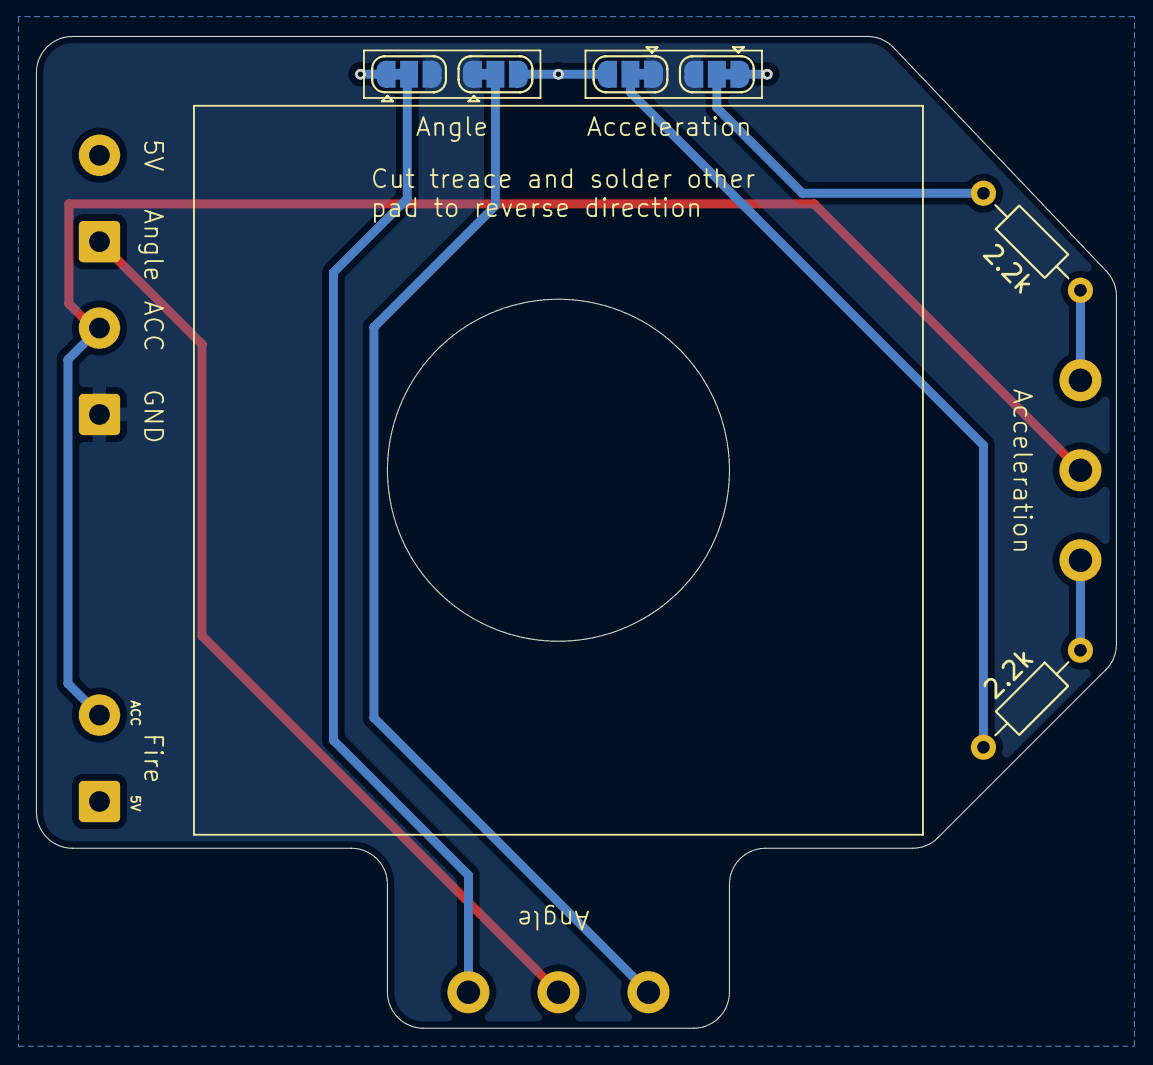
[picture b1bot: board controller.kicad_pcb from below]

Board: 2 copper layers, 60.0 x 55.1 mm, 11 parts (6 on the bottom side), 10 nets.

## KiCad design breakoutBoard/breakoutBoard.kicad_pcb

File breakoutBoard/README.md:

# AR11 Breakout Board for SPACEWAR

The cable that I made for the joysticks and screen got some wear and tear from being pulled out from one computer and installed in another and it was really tricky to get the cable in place when the systems was rackmounted.
To ease installation I designed a small breakout panel that can be rackmounted in the rear of the rack. It provided a 40 pin connector for connecting to the AR11 board in the PDP-11 computer. 

Then there are two DE9 connectors for the joysticks and one DA15 connector for the screen. The DA15 has the, X, Y and Z signals. Also included are the NON-STORE and ERASE signals which is needed when connecting a storage tube. I put three BNC connectors for the X, Y, Z signals in the case I want to use coaxial cables. To make it easy to adapt to different screens there are four jumpers on the board. These control the Z-output. There are two pairs. Each pair has one inverted and non-inverted sense. One pair is for the INTENSIFY signal which typically is used for point plotting. The other pair is taken from the CH02 DISP signal. This signal is just a logic level and can thus be used for drawing vectors.

The board has three mounting holes that will allow direct mounting to the rack cabinet.

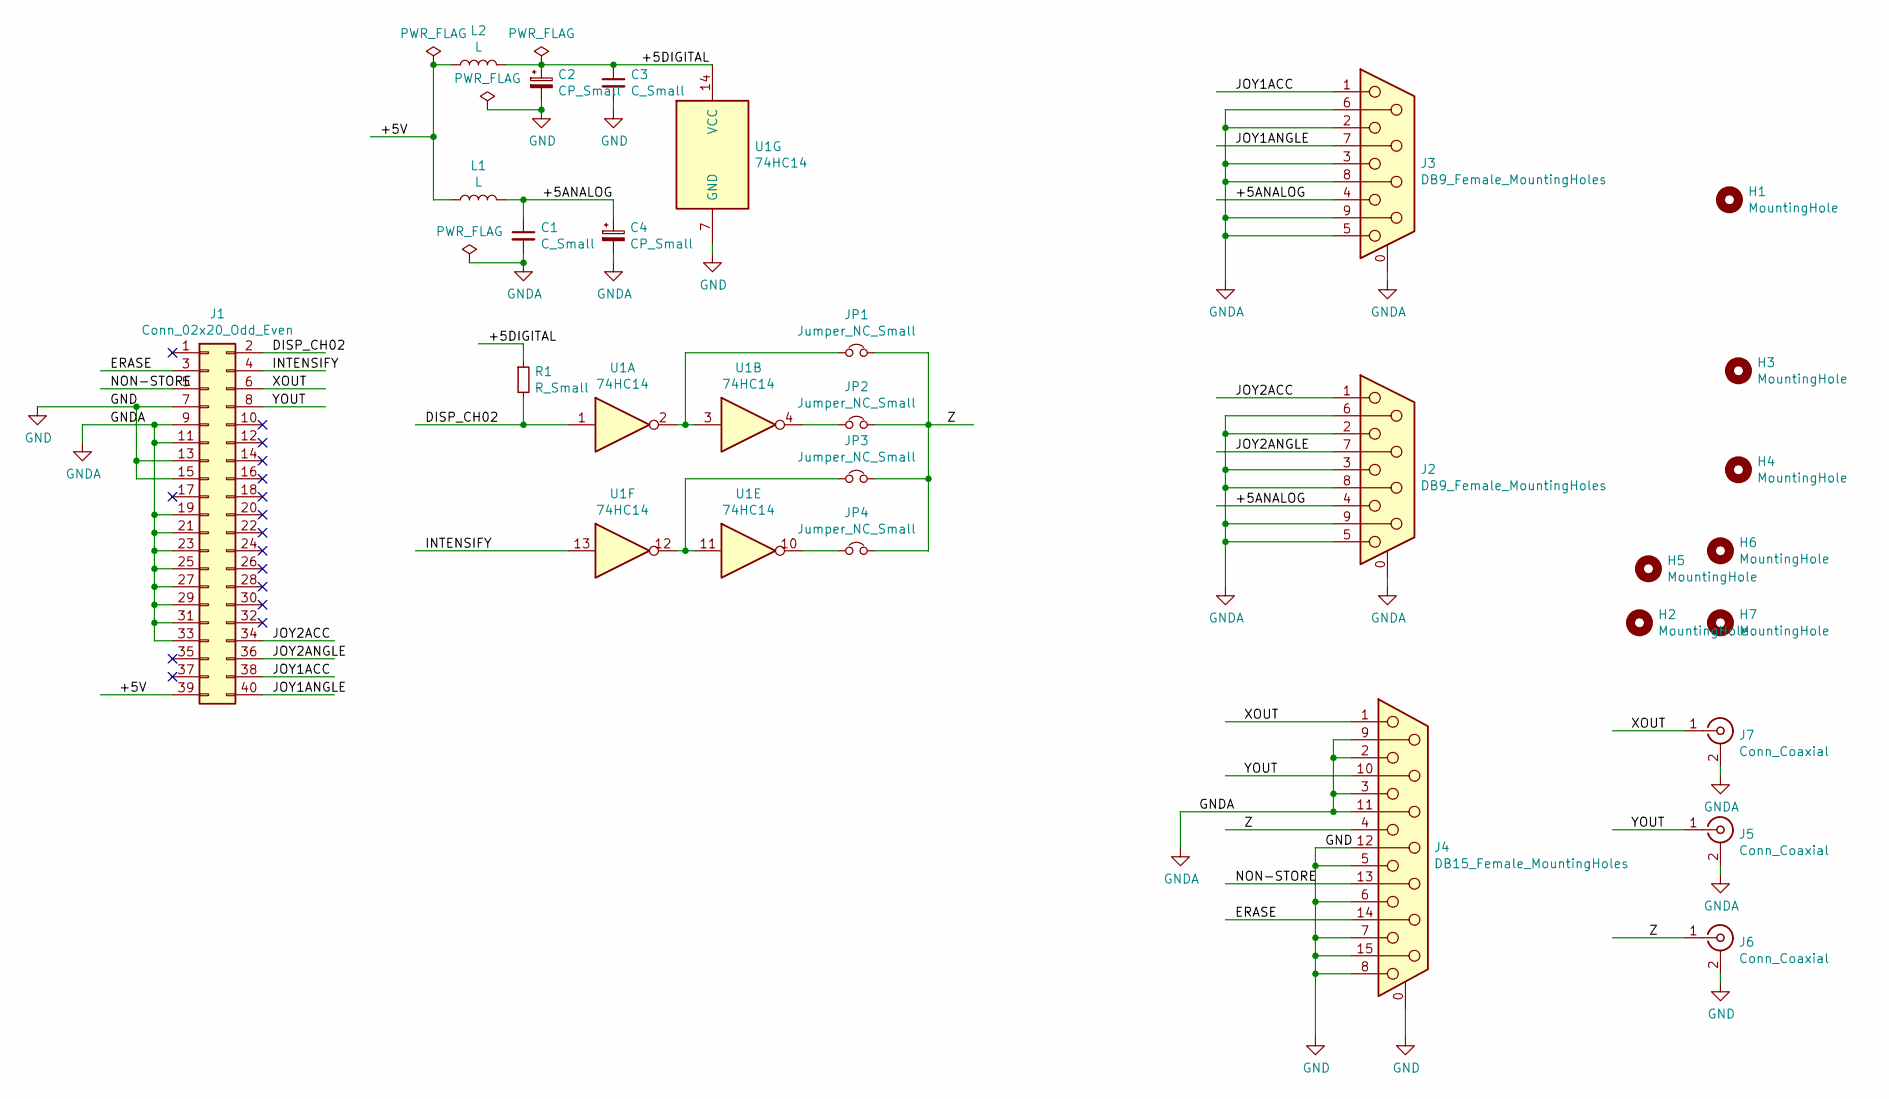
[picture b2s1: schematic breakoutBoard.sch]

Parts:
C1, C3: C_Small; C_Disc_D4.3mm_W1.9mm_P5.00mm
C2, C4: CP_Small; CP_Radial_D5.0mm_P2.50mm
H1, H3, H4: MountingHole; MountingHole_6.4mm_M6
H2, H5, H6, H7: MountingHole; MountingHole_3.2mm_M3
J1: Conn_02x20_Odd_Even; PinHeader_2x20_P2.54mm_Horizontal
J2, J3: DB9_Female_MountingHoles; DSUB-9_Female_Vertical_P2.77x2.84mm_MountingHoles
J4: DB15_Female_MountingHoles; DSUB-15_Female_Vertical_P2.77x2.84mm_MountingHoles
J5, J6, J7: Conn_Coaxial; BNC_TEConnectivity_1478204_Vertical
JP1, JP2, JP3, JP4: Jumper_NC_Small; PinHeader_1x02_P2.54mm_Vertical
L1, L2: L; L_Radial_D7.2mm_P3.00mm_MuRATA_1700
R1: R_Small; R_Axial_DIN0207_L6.3mm_D2.5mm_P10.16mm_Horizontal
U1: 74HC14; DIP-14_W7.62mm

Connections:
/+5ANALOG: C1.1, C4.1, J2.4, J3.4, L1.2
/+5DIGITAL: C2.1, C3.1, L2.2, R1.1, U1.14 (VCC)
/+5V: J1.39, L1.1, L2.1
/DISP_CH02: J1.2, R1.2, U1.1
/ERASE: J1.3, J4.14
/INTENSIFY: J1.4, U1.13
/JOY1ACC: J1.38, J3.1
/JOY1ANGLE: J1.40, J3.7
/JOY2ACC: J1.34, J2.1
/JOY2ANGLE: J1.36, J2.7
/NON-STORE: J1.5, J4.13
/XOUT: J1.6, J4.1, J7.1 (In)
/YOUT: J1.8, J4.10, J5.1 (In)
/Z: J4.4, J6.1 (In), JP1.2, JP2.2, JP3.2, JP4.2
GND: C2.2, C3.2, J1.7, J1.13, J1.15, J4.0 (PAD), J4.5, J4.6, J4.7, J4.8, J4.12, J4.15, J6.2 (Ext), U1.7 (GND)
GNDA: C1.2, C4.2, J1.9, J1.11, J1.19, J1.21, J1.23, J1.25, J1.27, J1.29, J1.31, J1.33, J2.0 (PAD), J2.2, J2.3, J2.5, J2.6, J2.8, J2.9, J3.0 (PAD), J3.2, J3.3, J3.5, J3.6, J3.8, J3.9, J4.2, J4.3, J4.9, J4.11 (P111), J5.2 (Ext), J7.2 (Ext)
unnamed: JP1.1, U1.2, U1.3
unnamed: JP2.1, U1.4
unnamed: JP3.1, U1.11, U1.12
unnamed: JP4.1, U1.10

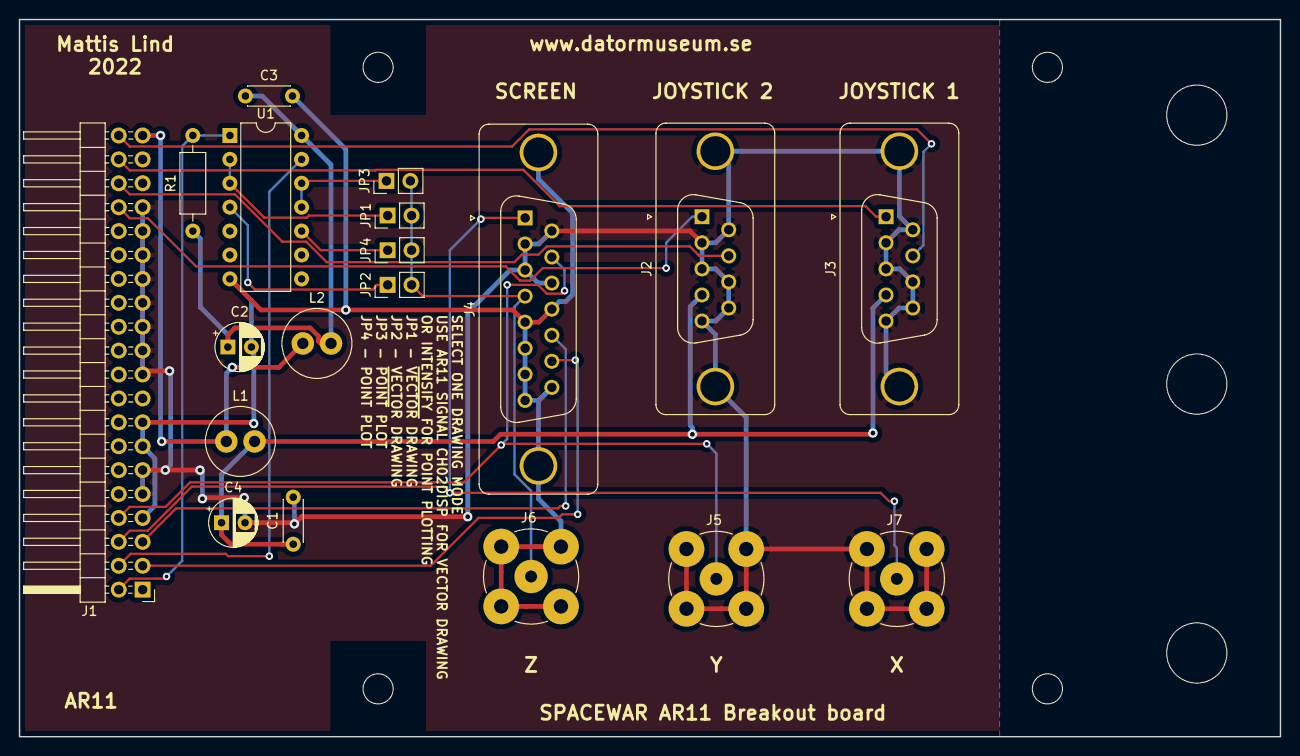
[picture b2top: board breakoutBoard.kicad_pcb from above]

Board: 2 copper layers, 134.0 x 76.2 mm, 26 parts (0 on the bottom side), 20 nets.

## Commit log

2019-01-02 First commit of all PDF, SRC (PAL). LST and OBJ as generated by PAL11-S
2019-01-02 First README file!
    First README file!
2019-01-03 Added FPMP-11 package, IOX-11 package and resulting SPACEWAR.ABS file
2019-01-03 Added a bit about linking and running
2019-01-03 Yet more on running..
2019-01-04 Added analysis on why the program halts.
2019-01-05 Added link to wiki page
2019-01-05 Fixed wrong address pf stack
2019-01-05 Added deposit to sr to cause PAL11-S better.
2019-01-06 Better description of link and asm process.
    Better description of the assembly and link process.
2019-01-06 Running
    More info on running the SPACE WAR program
2019-01-06 Added Absolute loader, PAL-11S assembler and LINK-11S linker
2019-01-06 Added section on AR11
2019-01-06 Spell fix
2019-01-06 Added links
2019-01-06 Didn't like ftp links.
2019-01-07 Discussion on dot drawing.
2020-01-10 Spelling fixes
2021-03-08 Spelling fixes.
2021-05-08 Fixing minor faults in the transcription.
2021-05-08 Some updates and clarifications to the build process
2021-05-08 Added wait for A/D conversion.
2021-05-09 Revert "Added wait for A/D conversion."
    This reverts commit 622b3cebdaecaac830ae60d7bb73504ab03b20f4.
2021-05-12 Built new version.
2021-05-12 SPCWAR module first.
2021-05-12 AR11 is not 2 complement.
2021-05-12 Patching for AR11.
2021-05-12 XOR instruction isn't in PDP-11/10 instruction set. Use ADD instead. Fixing error in label.
2021-05-12 New build.
2021-05-12 Built a binary with latest fixes.
2021-05-12 Set AD to unipolar and add offset 1000 octal (512 decimal) not 0400 (which is 256 decimal).
2022-01-22 Added a breakoutboard
2022-05-03 Changed from ERASE bit to CH02 bit
2022-05-03 Did the assembly.
2022-05-03 New binary using CH02 instead of ERASE signal.
2022-05-26 Added start-entry so that it automatically...
    .. starts when loaded
2022-05-26 Added a iox without the absolute loader end to be able to splice it with the spaceware binary.
2022-05-28 Added the IOX library to the build.
2022-05-28 Added info on IOX and transfer address.
2022-05-29 Changed to load low instead since most OSes loads high. Thus it should not interfere with any OS loaeded.
2022-05-29 The stack was growing downward from 200 and the stack limit is hard 400 so set address to 1000 instead.
2022-05-29 Added a DDDP TU58 image.
2022-05-30 Lowered priority level to allow for interrupts from the keyboard.
2023-03-15 Added info on how to do when using the dddp.dsk mage
2026-04-27 Added joystick PCB
2026-04-27 Small update to README
